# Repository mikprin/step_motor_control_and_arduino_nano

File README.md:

# step_motor_control_and_arduino_nano
Steper motor control with arduino nano for Skoltech
This project implements simple PCB for soldering arduino nano to stepper motor using standard stepper motor driver module such as DRV8825.

You can find a schematic [here](out/sch/pump_driver.pdf). Design optimized for minimal soldering (for lazy students). Also you can find ready gerbers in release.

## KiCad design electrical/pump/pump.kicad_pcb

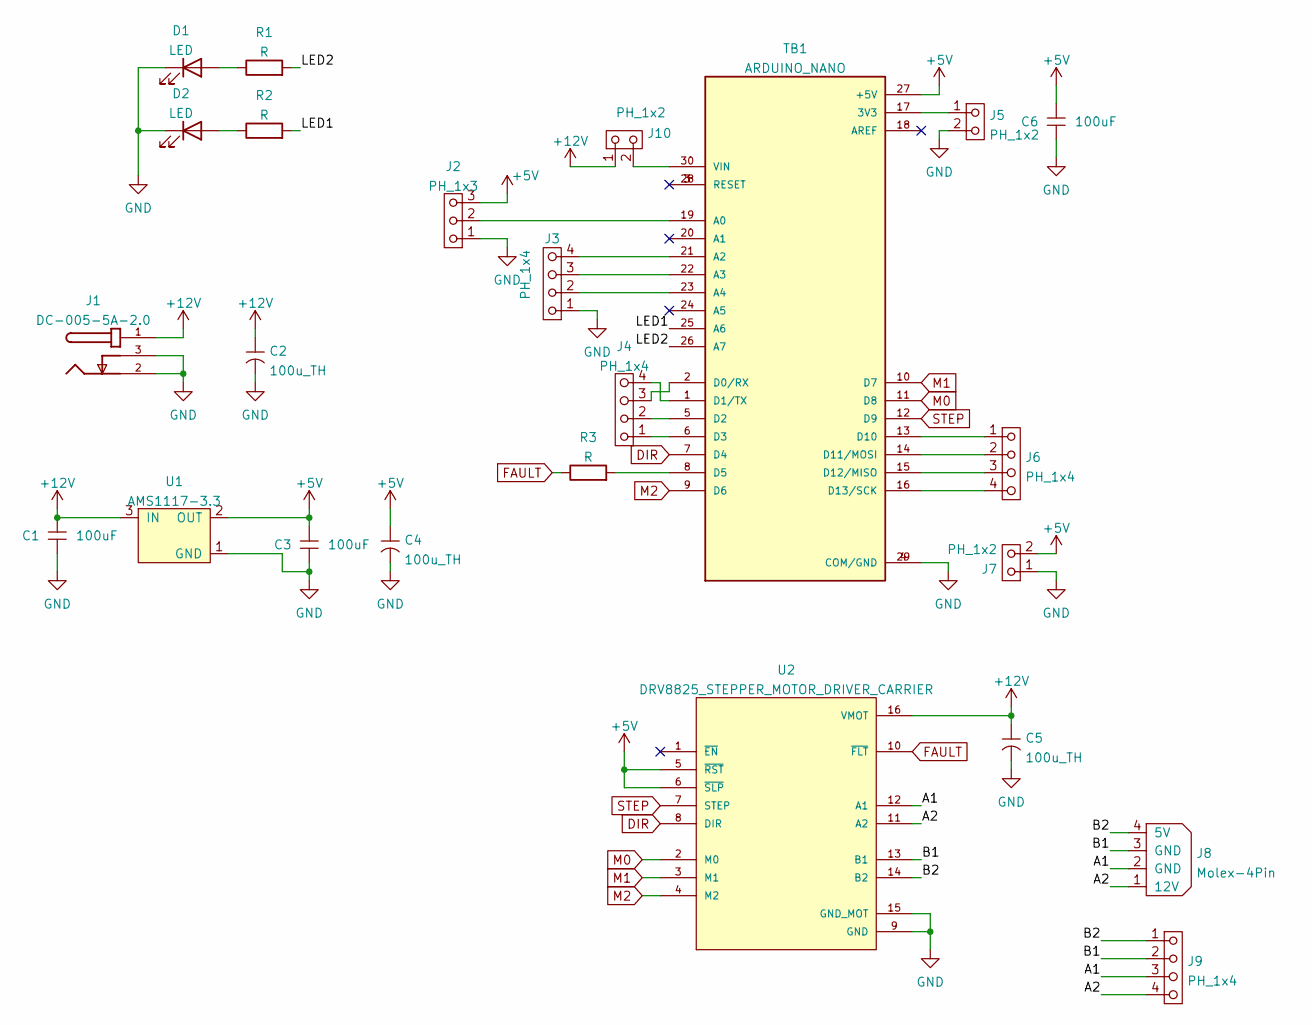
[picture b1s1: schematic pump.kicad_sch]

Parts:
C1, C3, C6: 100uF; 1206_Passive
C2, C4, C5: 100u_TH; CAP-EL-RADIAL-6.3X12; MFR# RVT1V101M0607
D1, D2: LED; PinHeader_1x2_Generic
J1: DC-005-5A-2.0; XKB_DC-005-5A-2.0; PARTREV A0
J2: PH_1x3; PinHeader_1x3_Generic
J3, J4, J6, J9: PH_1x4; PinHeader_1x4
J5, J7, J10: PH_1x2; PinHeader_1x2_Generic
J8: Molex-4Pin; MOLEX_8981_4-PIN
R1, R2, R3: R; PinHeader_1x2_Generic
TB1: ARDUINO_NANO; SHIELD_ARDUINO_NANO
U1: AMS1117-3.3; SOT229P700X180-4N
U2: DRV8825_STEPPER_MOTOR_DRIVER_CARRIER; IC_DRV8825_STEPPER_MOTOR_DRIVER_CARRIER

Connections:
+5V: C3.1, C4.+, C6.1, J2.3, J7.2, TB1.27 (+5V), U1.2 (OUT), U1.4 (OUT), U2.5 (~RST), U2.6 (~SLP)
+12V: C1.1, C2.+, C5.+, J1.1, J10.1, U1.3 (IN), U2.16 (VMOT)
/A1: J8.2 (GND), J9.3, U2.12 (A1)
/A2: J8.1 (12V), J9.4, U2.11 (A2)
/B1: J8.3 (GND), J9.2, U2.13 (B1)
/B2: J8.4 (5V), J9.1, U2.14 (B2)
/LED1: R2.2, TB1.25 (A6)
/LED2: R1.2, TB1.26 (A7)
DIR: TB1.7 (D4), U2.8 (DIR)
FAULT: R3.1, U2.10 (~FLT)
GND: C1.2, C2.-, C3.2, C4.-, C5.-, C6.2, D1.1 (K), D2.1 (K), J1.2, J1.3, J2.1, J3.1, J5.2, J7.1, TB1.4 (COM/GND), TB1.29 (COM/GND), U1.1 (GND), U2.9 (GND), U2.15 (GND_MOT)
M0: TB1.11 (D8), U2.2 (M0)
M1: TB1.10 (D7), U2.3 (M1)
M2: TB1.9 (D6), U2.4 (M2)
unnamed: D1.2 (A), R1.1
unnamed: D2.2 (A), R2.1
unnamed: J2.2, TB1.19 (A0)
unnamed: J3.2, TB1.23 (A4)
unnamed: J3.3, TB1.22 (A3)
unnamed: J3.4, TB1.21 (A2)
unnamed: J4.1, TB1.6 (D3)
unnamed: J4.2, TB1.5 (D2)
unnamed: J4.3, TB1.2 (D0/RX)
unnamed: J4.4, TB1.1 (D1/TX)
unnamed: J5.1, TB1.17 (3V3)
unnamed: J6.1, TB1.13 (D10)
unnamed: J6.2, TB1.14 (D11/MOSI)
unnamed: J6.3, TB1.15 (D12/MISO)
unnamed: J6.4, TB1.16 (D13/SCK)
unnamed: R3.2, TB1.8 (D5)
unnamed: J10.2, TB1.30 (VIN)
STEP: TB1.12 (D9), U2.7 (STEP)

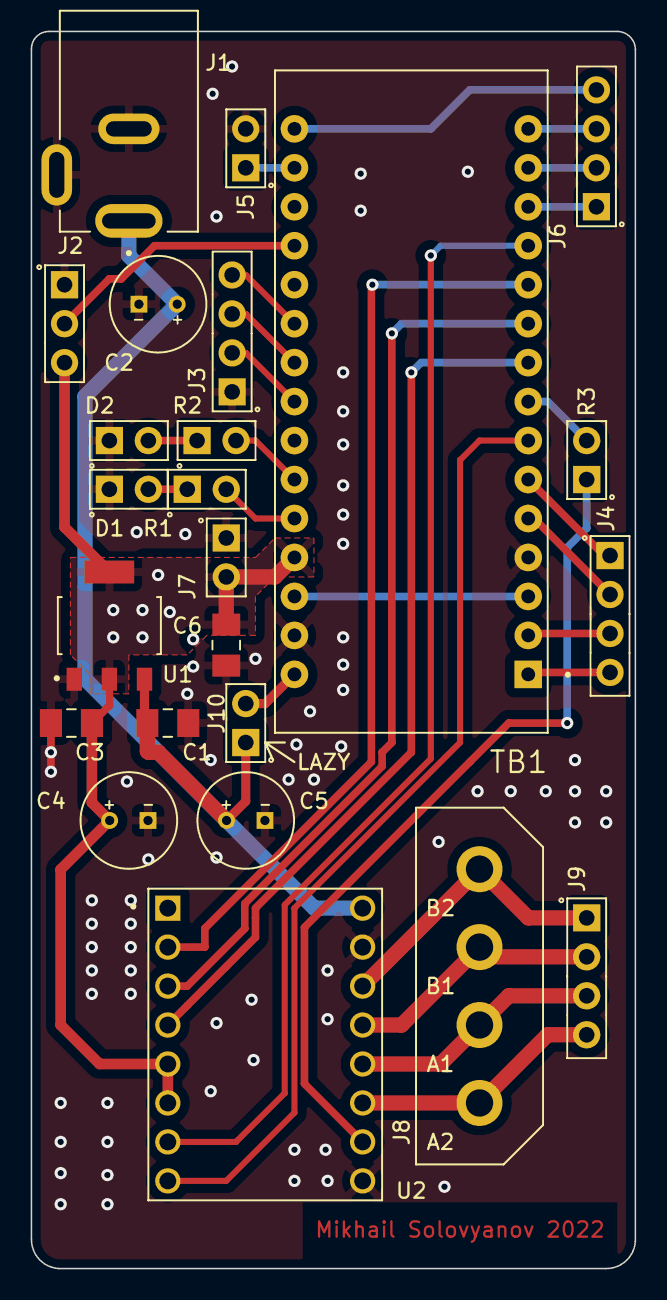
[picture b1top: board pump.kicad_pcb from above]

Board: 2 copper layers, 39.4 x 80.6 mm, 24 parts (0 on the bottom side), 32 nets.

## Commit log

2022-01-30 init
2022-01-30 rem zips
2022-02-03 removed outputs
2022-02-03 some changes or not
